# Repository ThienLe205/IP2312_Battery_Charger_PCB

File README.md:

# IP2312_Battery_Charger_PCB
Open-Source Battery Charger Module for PCB SUMMER 2026 - FETEL

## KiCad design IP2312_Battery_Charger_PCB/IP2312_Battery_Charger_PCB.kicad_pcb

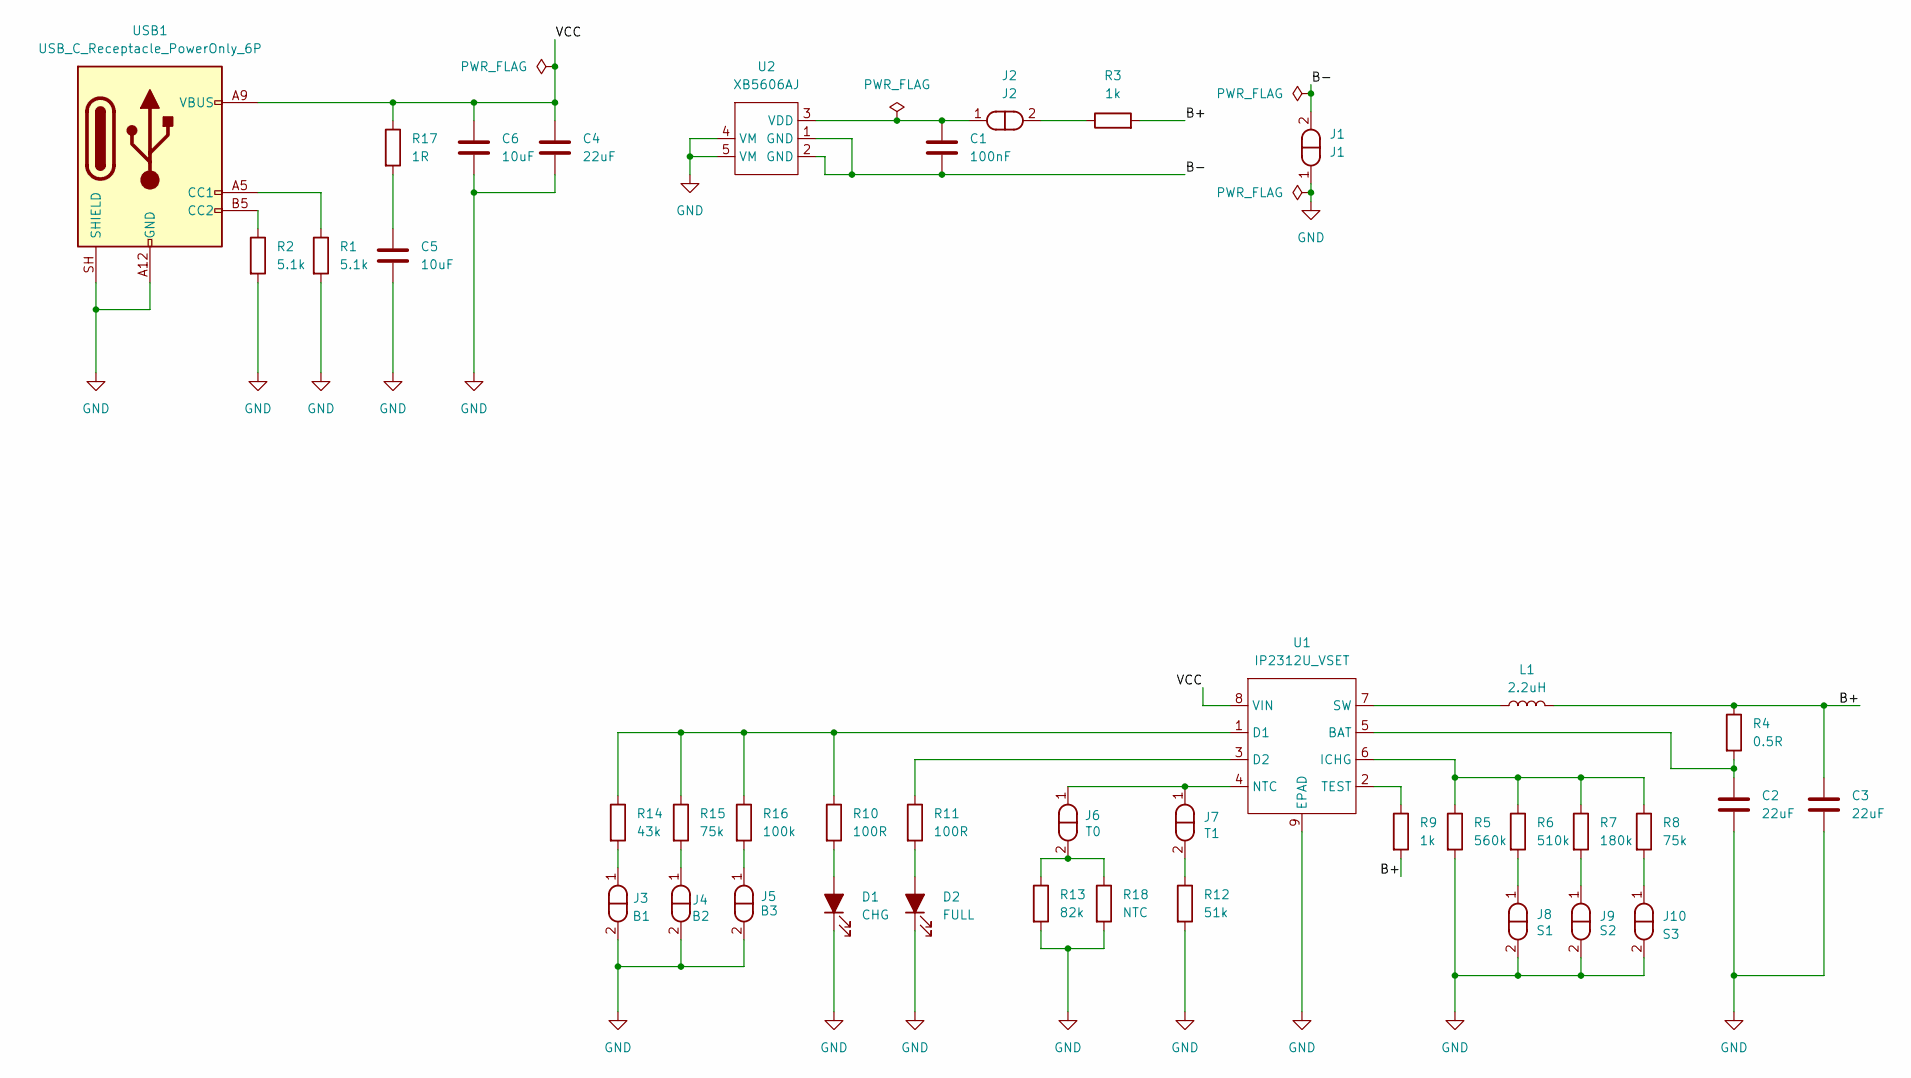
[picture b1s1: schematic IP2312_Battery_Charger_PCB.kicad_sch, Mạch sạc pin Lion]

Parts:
C1: 100nF; C_0402_1005Metric
C2, C3, C4: 22uF; C_0805_2012Metric
C5, C6: 10uF; C_0805_2012Metric
D1: CHG; LED_0603_1608Metric
D2: FULL; LED_0603_1608Metric
J1: J1; Jumper_0603_1608Metric
J2: J2; Jumper_0603_1608Metric
J3: B1; Jumper_0603_1608Metric
J4: B2; Jumper_0603_1608Metric
J5: B3; Jumper_0603_1608Metric
J6: T0; Jumper_0603_1608Metric
J7: T1; Jumper_0603_1608Metric
J8: S1; Jumper_0603_1608Metric
J9: S2; Jumper_0603_1608Metric
J10: S3; Jumper_0603_1608Metric
L1: 2.2uH; L_Sunlord_MWSA0603S
R1, R2: 5.1k; R_0402_1005Metric
R3, R9: 1k; R_0603_1608Metric
R4: 0.5R; R_0603_1608Metric
R5: 560k; R_0603_1608Metric
R6: 510k; R_0603_1608Metric
R7: 180k; R_0603_1608Metric
R8, R15: 75k; R_0603_1608Metric
R10, R11: 100R; R_0603_1608Metric
R12: 51k; R_0603_1608Metric
R13: 82k; R_0603_1608Metric
R14: 43k; R_0603_1608Metric
R16: 100k; R_0603_1608Metric
R17: 1R; R_0603_1608Metric
R18: NTC; R_0603_1608Metric
U1: IP2312U_VSET; HSOP-8-1EP_3.9x4.9mm_P1.27mm_EP2.3x2.3mm_ThermalVias-IP2312
U2: XB5606AJ; SOT-23-5-XB5606AJ
USB1: USB_C_Receptacle_PowerOnly_6P; USB-C_Receptacle_GCT_USB4125-xx-x-0190_6P_TopMnt_Horizontal

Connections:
/B+: C3.1, L1.2, R3.2, R4.1, R9.2
/B-: C1.1, J1.2, U2.1 (GND), U2.2 (GND)
/VCC: C4.1, C6.1, R17.1, U1.8 (VIN), USB1.A9 (VBUS), USB1.B9 (VBUS)
GND: C2.2, C3.2, C4.2, C5.2, C6.2, D1.1 (K), D2.1 (K), J1.1, J3.2, J4.2, J5.2, J8.2, J9.2, J10.2, R1.2, R2.2, R5.2, R12.2, R13.2, R18.2, U1.9 (EPAD), U2.4 (VM), U2.5 (VM), USB1.A12 (GND), USB1.B12 (GND), USB1.SH (SHIELD)
unnamed: C5.1, R17.2
unnamed: D1.2 (A), R10.2
unnamed: D2.2 (A), R11.2
unnamed: J2.2, R3.1
unnamed: J3.1, R14.2
unnamed: J4.1, R15.2
unnamed: J5.1, R16.2
unnamed: J6.2, R13.1, R18.1
unnamed: J7.2, R12.1
unnamed: J8.1, R6.2
unnamed: J9.1, R7.2
unnamed: J10.1, R8.2
unnamed: C2.1, R4.2, U1.5 (BAT)
unnamed: R10.1, R14.1, R15.1, R16.1, U1.1 (D1)
unnamed: R11.1, U1.3 (D2)
unnamed: R5.1, R6.1, R7.1, R8.1, U1.6 (ICHG)
unnamed: J6.1, J7.1, U1.4 (NTC)
unnamed: L1.1, U1.7 (SW)
unnamed: R9.1, U1.2 (TEST)
unnamed: C1.2, J2.1, U2.3 (VDD)
unnamed: R1.1, USB1.A5 (CC1)
unnamed: R2.1, USB1.B5 (CC2)

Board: 2 copper layers, 40 parts (0 on the bottom side), 26 nets, no tracks yet.
